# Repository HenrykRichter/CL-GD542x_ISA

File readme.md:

# Project  Cirrus Logic 542x ISA video card
This project is a fork of [542x_ISA](https://github.com/matt1187/542x_ISA) with some tweaks
and additions to the PCB. Notable changes compared to original project:
- made room on PCB to place the RAMs in SMT sockets
- added Monitor ID option (static or by attached Monitor)

Remaking from Cirrus Logic Databook  "CL-GD542X_Technical_Reference_Manual_Jan1994"

# PCB Revision History 
- forked from revision 001
- CL-GD542x-003 initial upload

# Features
- Cirrus Logic (CL-GD5422-5429) video chipset (5420 is not recommend for this design)
- good chocie video card for ISA bus platform
- up to 2 MB DRAM
- 80 MHz integrated RAMDAC (GD5429: 86 MHz )
- Win 3.1, Win9x, Win NT 3.51 & 4 driver available
- cheap GD542x VLB card as compoment donor.
- cheap 2 layer PCB layout 
  
# Issues 
- some 542x chip has vertical noise/stripe on TFT. (It is not pcb issuses)
- ROM from  cirrus logic video card as donor is not usable (hi/lo byte is seperated to difference address space, like address line "A0 and A14" is swapped)
- in some cases, the GD542x will boot in Monochrome mode. See [here](https://forum.vcfed.org/index.php?threads/trident-card-that-thinks-colour-monitor-is-monochrome.79054) for a fix.

# notes
- GD5420/22/24 support only 1 MB DRAM
- U11 & U12  is first 1 MB , U13/14 is seconds MB (except 5420, only U12 and U14 )
- all component with  followed ID is config strap (R55, R57, R59, R61, R63, R69, R73) place all **except** R55, R69
- R15 don't place, if you using interal XTAL oscillator (Y1/Y2 , C39,C40)
- Place only one of Y1/Y2 (either SMD **or** HC-49)
- SPI-EEPROM is optional.

# Bill of material

- see BOM subfolder for an iBOM file

# driver & ROM 
- []

# License
The project is free for non-commercial reproduction. Do not sell it on Ebay or other platforms for profit. Do not make a closed source derivative. Share your experiences and ideas with the community.

This work is licensed under a [Creative Commons Attribution-NonCommercial-ShareAlike 4.0 International License][cc-by-nc-sa].

[![CC BY-NC-SA 4.0][cc-by-nc-sa-image]][cc-by-nc-sa]

[cc-by-nc-sa]: http://creativecommons.org/licenses/by-nc-sa/4.0/
[cc-by-nc-sa-image]: https://licensebuttons.net/l/by-nc-sa/4.0/88x31.png

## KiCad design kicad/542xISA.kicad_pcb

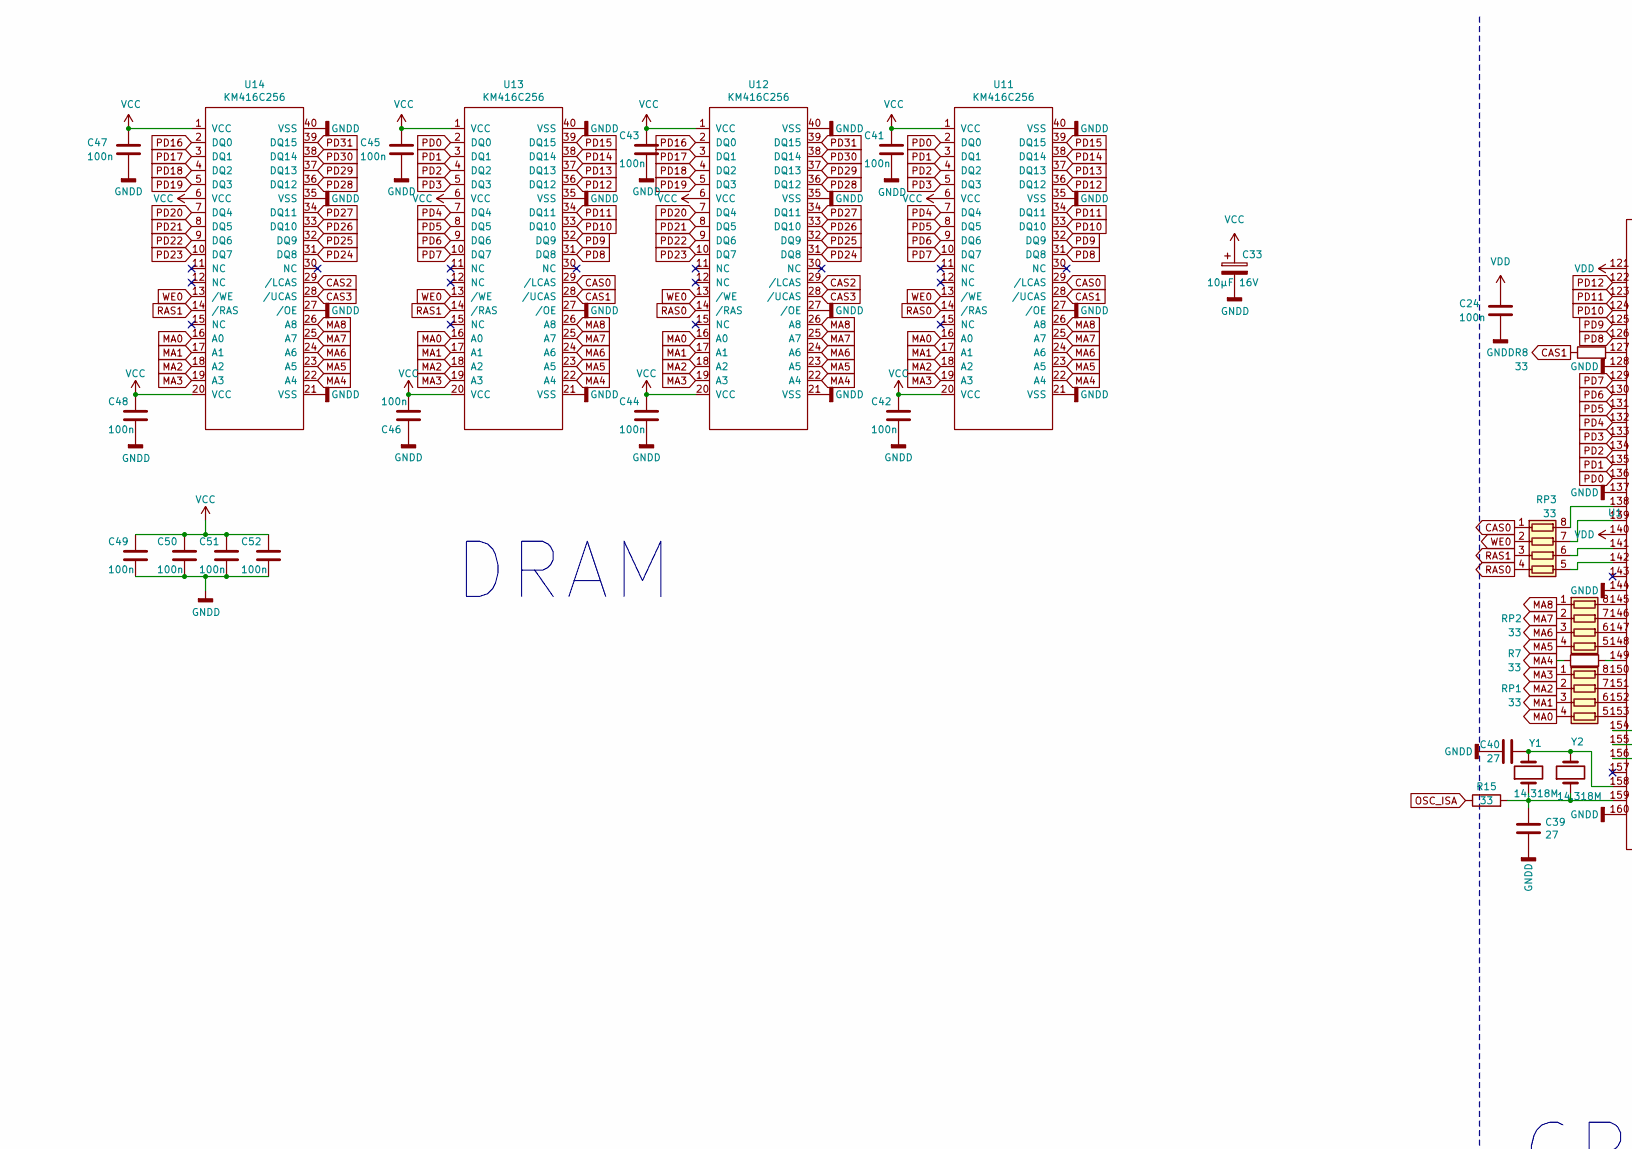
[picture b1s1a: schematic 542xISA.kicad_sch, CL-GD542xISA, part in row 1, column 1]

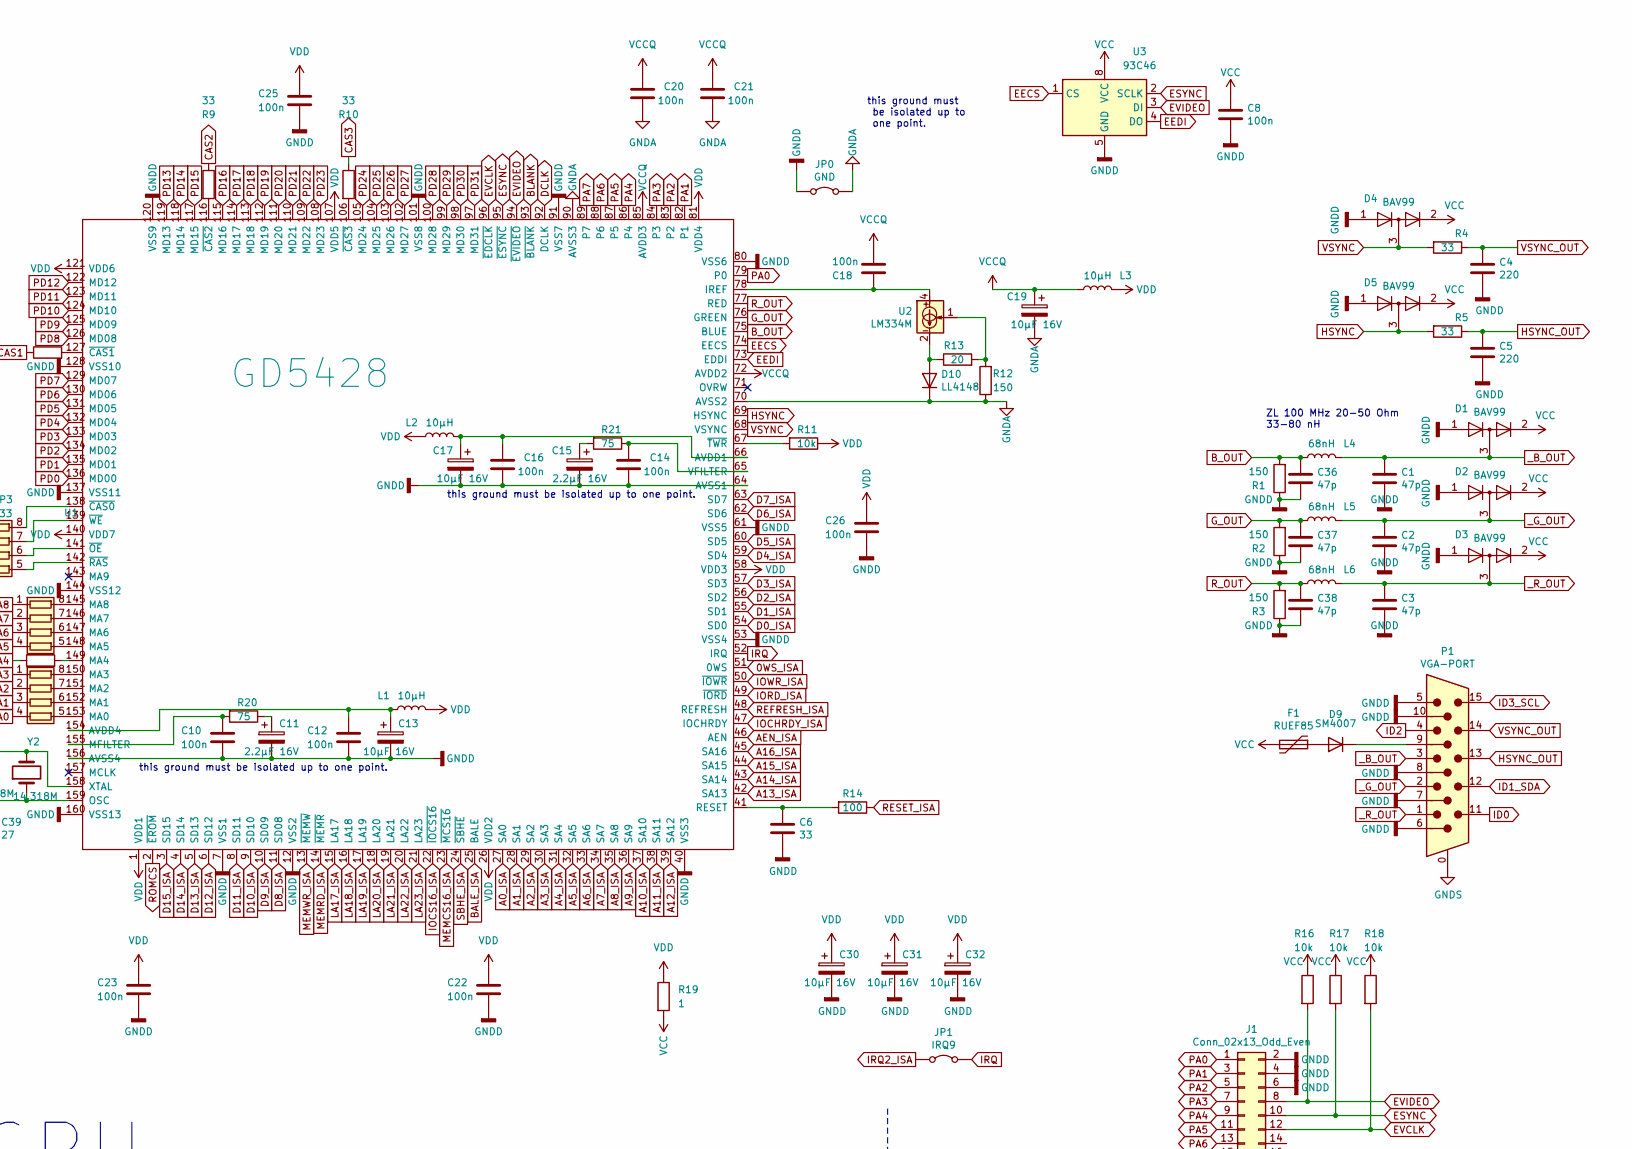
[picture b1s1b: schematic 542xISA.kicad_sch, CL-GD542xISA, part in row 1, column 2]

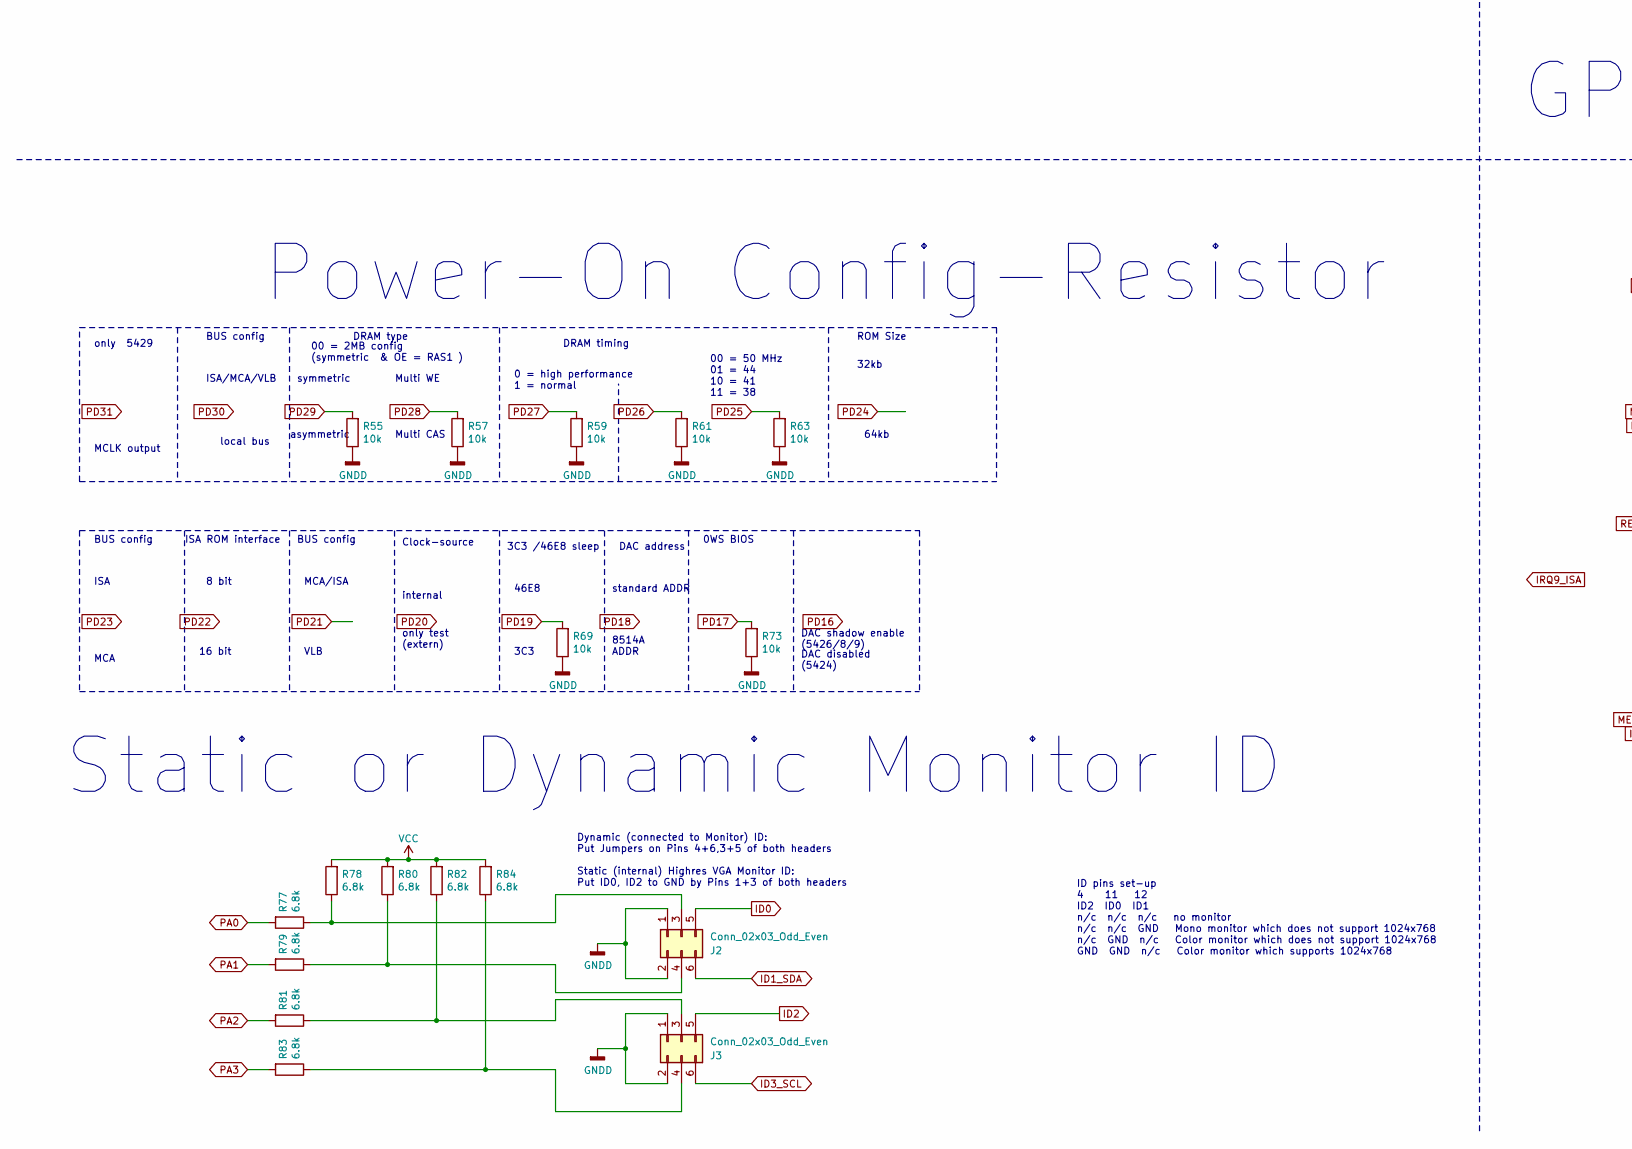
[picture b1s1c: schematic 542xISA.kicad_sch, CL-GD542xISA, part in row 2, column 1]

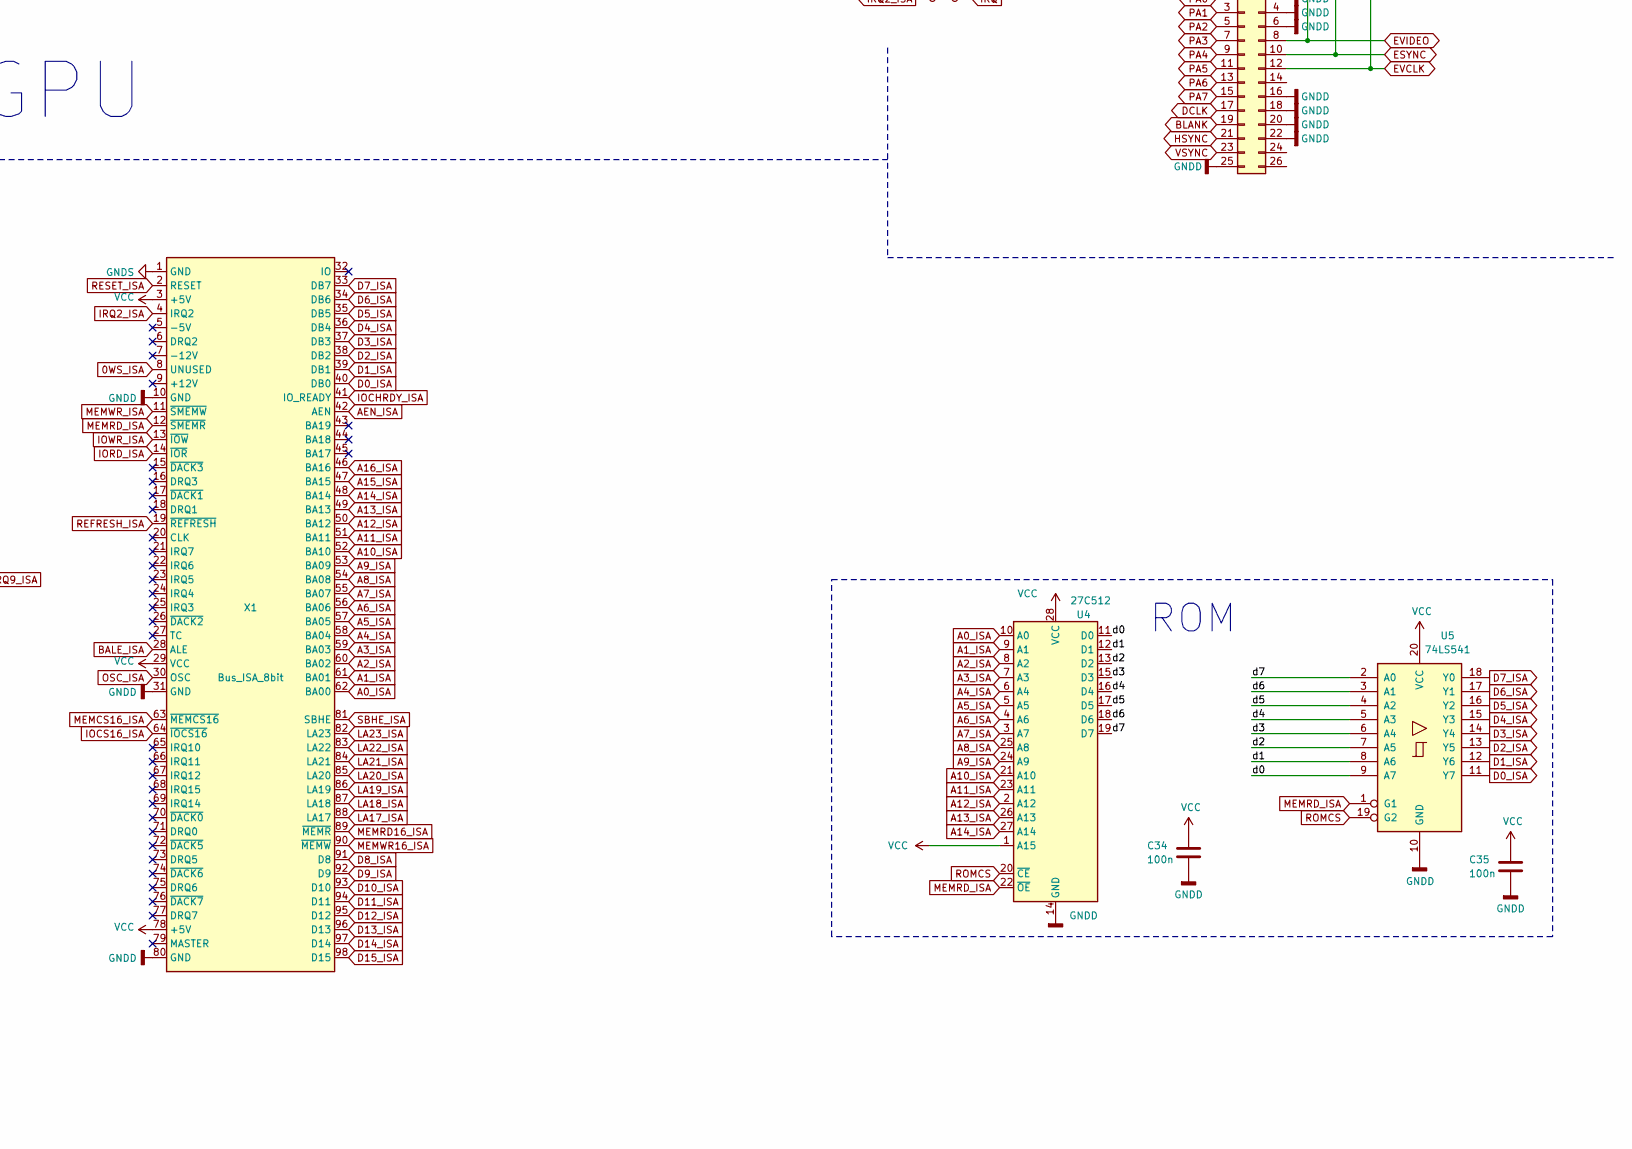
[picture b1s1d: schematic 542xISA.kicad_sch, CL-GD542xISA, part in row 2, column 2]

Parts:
C1, C2, C3, C36, C37, C38: 47p; C_0805_2012Metric
C4, C5: 220; C_0805_2012Metric
C6: 33; C_0805_2012Metric
C8, C10, C12, C14, C16, C18, C20, C21, C22, C23, C24, C25, C26, C34, C35, C41, C42, C43, C44, C45, C46, C47, C48, C49, C50, C51, C52: 100n; C_0805_2012Metric
C11, C15: 2.2µF 16V; CP_EIA-3528-12_Kemet-T
C13, C17, C19, C31, C32: 10µF 16V; CP_EIA-6032-15_Kemet-U
C30, C33: 10µF 16V; C_0805_2012Metric_Pad1.18x1.45mm_HandSolder
C39, C40: 27; C_0805_2012Metric
D1, D2, D3, D4, D5: BAV99; SOT-23
D9: SM4007; D_MELF
D10: LL4148; D_MiniMELF
F1: RUEF85; Fuse_Bourns_MF-RG300
J1: Conn_02x13_Odd_Even; PinHeader_2x13_P2.54mm_Vertical
J2, J3: Conn_02x03_Odd_Even; PinHeader_2x03_P2.54mm_Vertical
JP0: GND; SolderJumper-2_P1.3mm_Bridged2Bar_Pad1.0x1.5mm
JP1: IRQ9; PinHeader_1x02_P2.54mm_Vertical
L1, L2, L3: 10µH; L_0805_2012Metric
L4, L5, L6: 68nH; L_1206_3216Metric
P1: VGA-PORT; DSUB-15-HD_Female_Horizontal_P2.29x1.98mm_EdgePinOffset8.35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
R1, R2, R3, R12: 150; R_0805_2012Metric
R4, R5, R7, R8, R9, R10, R15: 33; R_0805_2012Metric
R11, R16, R17, R18, R55, R57, R59, R61, R63, R69, R73: 10k; R_0805_2012Metric
R13: 20; R_0805_2012Metric
R14: 100; R_0805_2012Metric
R19: 1; R_0805_2012Metric
R20, R21: 75; R_0805_2012Metric
R77, R78, R79, R80, R81, R82, R83, R84: 6.8k; R_0805_2012Metric
RP1, RP2, RP3: 33; R_Array_Concave_4x0603
U1: GD5428; PQFP-160_28x28mm_P0.65mm
U2: LM334M; SOIC-8_3.9x4.9mm_P1.27mm
U3: 93C46; SOIC-8_3.9x4.9mm_P1.27mm
U4: 27C512; DIP-28_W15.24mm_Socket
U5: 74LS541; SOIC-20W_7.5x12.8mm_P1.27mm
U11, U12, U13, U14: KM416C256; SOJ-40-Socket
X1: Bus_ISA_8bit; BUS_AT
Y1: 14.318M; Crystal_SMD_0603-2Pin_6.0x3.5mm
Y2: 14.318M; Crystal_HC49-U_Vertical

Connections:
0WS_ISA: U1.51 (0WS), X1.8 (UNUSED)
/d0: U4.11 (D0), U5.9 (A7)
/d1: U4.12 (D1), U5.8 (A6)
/d2: U4.13 (D2), U5.7 (A5)
/d3: U4.15 (D3), U5.6 (A4)
/d4: U4.16 (D4), U5.5 (A3)
/d5: U4.17 (D5), U5.4 (A2)
/d6: U4.18 (D6), U5.3 (A1)
/d7: U4.19 (D7), U5.2 (A0)
A0_ISA: U1.27 (SA0), U4.10 (A0), X1.62 (BA00)
A1_ISA: U1.28 (SA1), U4.9 (A1), X1.61 (BA01)
A2_ISA: U1.29 (SA2), U4.8 (A2), X1.60 (BA02)
A3_ISA: U1.30 (SA3), U4.7 (A3), X1.59 (BA03)
A4_ISA: U1.31 (SA4), U4.6 (A4), X1.58 (BA04)
A5_ISA: U1.32 (SA5), U4.5 (A5), X1.57 (BA05)
A6_ISA: U1.33 (SA6), U4.4 (A6), X1.56 (BA06)
A7_ISA: U1.34 (SA7), U4.3 (A7), X1.55 (BA07)
A8_ISA: U1.35 (SA8), U4.25 (A8), X1.54 (BA08)
A9_ISA: U1.36 (SA9), U4.24 (A9), X1.53 (BA09)
A10_ISA: U1.37 (SA10), U4.21 (A10), X1.52 (BA10)
A11_ISA: U1.38 (SA11), U4.23 (A11), X1.51 (BA11)
A12_ISA: U1.39 (SA12), U4.2 (A12), X1.50 (BA12)
A13_ISA: U1.42 (SA13), U4.26 (A13), X1.49 (BA13)
A14_ISA: U1.43 (SA14), U4.27 (A14), X1.48 (BA14)
A15_ISA: U1.44 (SA15), X1.47 (BA15)
A16_ISA: U1.45 (SA16), X1.46 (BA16)
AEN_ISA: U1.46 (AEN), X1.42 (AEN)
BALE_ISA: U1.25 (BALE), X1.28 (ALE)
BLANK: J1.19, U1.93 (~BLANK)
B_OUT: C36.1, L4.2, R1.2, U1.75 (BLUE)
CAS0: RP3.1 (R1.1), U11.29 (/LCAS), U13.29 (/LCAS)
CAS1: R8.1, U11.28 (/UCAS), U13.28 (/UCAS)
CAS2: R9.1, U12.29 (/LCAS), U14.29 (/LCAS)
CAS3: R10.1, U12.28 (/UCAS), U14.28 (/UCAS)
D0_ISA: U1.54 (SD0), U5.11 (Y7), X1.40 (DB0)
D1_ISA: U1.55 (SD1), U5.12 (Y6), X1.39 (DB1)
D2_ISA: U1.56 (SD2), U5.13 (Y5), X1.38 (DB2)
D3_ISA: U1.57 (SD3), U5.14 (Y4), X1.37 (DB3)
D4_ISA: U1.59 (SD4), U5.15 (Y3), X1.36 (DB4)
D5_ISA: U1.60 (SD5), U5.16 (Y2), X1.35 (DB5)
D6_ISA: U1.62 (SD6), U5.17 (Y1), X1.34 (DB6)
D7_ISA: U1.63 (SD7), U5.18 (Y0), X1.33 (DB7)
D8_ISA: U1.11 (SD08), X1.91 (D8)
D9_ISA: U1.10 (SD09), X1.92 (D9)
D10_ISA: U1.9 (SD10), X1.93 (D10)
D11_ISA: U1.8 (SD11), X1.94 (D11)
D12_ISA: U1.6 (SD12), X1.95 (D12)
D13_ISA: U1.5 (SD13), X1.96 (D13)
D14_ISA: U1.4 (SD14), X1.97 (D14)
D15_ISA: U1.3 (SD15), X1.98 (D15)
DCLK: J1.17, U1.92 (DCLK)
EECS: U1.74 (EECS), U3.1 (CS)
EEDI: U1.73 (EDDI), U3.4 (DO)
ESYNC: J1.10, R17.2, U1.95 (~ESYNC), U3.2 (SCLK)
EVCLK: J1.12, R18.2, U1.96 (~EDCLK)
EVIDEO: J1.8, R16.2, U1.94 (~EVIDEO), U3.3 (DI)
GNDA: C19.2, C20.2, C21.2, D10.1 (K), JP0.2 (B), R12.1, U1.70 (AVSS2), U1.90 (AVSS3)
GNDD: C1.2, C2.2, C3.2, C4.2, C5.2, C6.2, C8.2, C10.2, C11.2, C12.2, C13.2, C14.2, C15.2, C16.2, C17.2, C22.2, C23.2, C24.2, C25.2, C26.2, C30.2, C31.2, C32.2, C33.2, C34.2, C35.2, C36.2, C37.2, C38.2, C39.2, C40.1, C41.2, C42.2, C43.2, C44.2, C45.2, C46.2, C47.2, C48.2, C49.2, C50.2, C51.2, C52.2, D1.1 (K), D2.1 (K), D3.1 (K), D4.1 (K), D5.1 (K), J1.2, J1.4, J1.6, J1.16, J1.18, J1.20, J1.22, J1.25, J2.1, J2.2, J3.1, J3.2, JP0.1 (A), P1.5, P1.6, P1.7, P1.8, P1.10, R1.1, R2.1, R3.1, R55.1, R57.1, R59.1, R61.1, R63.1, R69.1, R73.1, U1.7 (VSS1), U1.12 (VSS2), U1.40 (VSS3), U1.53 (VSS4), U1.61 (VSS5), U1.64 (AVSS1), U1.80 (VSS6), U1.91 (VSS7), U1.101 (VSS8), U1.120 (VSS9), U1.128 (VSS10), U1.137 (VSS11), U1.144 (VSS12), U1.156 (AVSS4), U1.160 (VSS13), U3.5 (GND), U4.14 (GND), U5.10 (GND), U11.21 (VSS), U11.27 (/OE), U11.35 (VSS), U11.40 (VSS), U12.21 (VSS), U12.27 (/OE), U12.35 (VSS), U12.40 (VSS), U13.21 (VSS), U13.27 (/OE), U13.35 (VSS), U13.40 (VSS), U14.21 (VSS), U14.27 (/OE), U14.35 (VSS), U14.40 (VSS), X1.10 (GND), X1.31 (GND), X1.80 (GND)
GNDS: P1.0, X1.1 (GND)
G_OUT: C37.1, L5.2, R2.2, U1.76 (GREEN)
HSYNC: D5.3 (K), J1.21, R5.2, U1.69 (HSYNC)
HSYNC_OUT: C5.1, P1.13, R5.1
ID0: J2.5, P1.11
ID1_SDA: J2.6, P1.12
ID2: J3.5, P1.4
ID3_SCL: J3.6, P1.15
IOCHRDY_ISA: U1.47 (IOCHRDY), X1.41 (IO_READY)
IOCS16_ISA: U1.22 (~IOCS16), X1.64 (~IOCS16)
IORD_ISA: U1.49 (~IORD), X1.14 (~IOR)
IOWR_ISA: U1.50 (~IOWR), X1.13 (~IOW)
IRQ: JP1.2 (B), U1.52 (IRQ)
IRQ2_ISA: JP1.1 (A), X1.4 (IRQ2)
LA17_ISA: U1.15 (LA17), X1.88 (LA17)
LA18_ISA: U1.16 (LA18), X1.87 (LA18)
LA19_ISA: U1.17 (LA19), X1.86 (LA19)
LA20_ISA: U1.18 (LA20), X1.85 (LA20)
LA21_ISA: U1.19 (LA21), X1.84 (LA21)
LA22_ISA: U1.20 (LA22), X1.83 (LA22)
LA23_ISA: U1.21 (LA23), X1.82 (LA23)
MA0: RP1.4 (R4.1), U11.16 (A0), U12.16 (A0), U13.16 (A0), U14.16 (A0)
MA1: RP1.3 (R3.1), U11.17 (A1), U12.17 (A1), U13.17 (A1), U14.17 (A1)
MA2: RP1.2 (R2.1), U11.18 (A2), U12.18 (A2), U13.18 (A2), U14.18 (A2)
MA3: RP1.1 (R1.1), U11.19 (A3), U12.19 (A3), U13.19 (A3), U14.19 (A3)
MA4: R7.1, U11.22 (A4), U12.22 (A4), U13.22 (A4), U14.22 (A4)
MA5: RP2.4 (R4.1), U11.23 (A5), U12.23 (A5), U13.23 (A5), U14.23 (A5)
MA6: RP2.3 (R3.1), U11.24 (A6), U12.24 (A6), U13.24 (A6), U14.24 (A6)
MA7: RP2.2 (R2.1), U11.25 (A7), U12.25 (A7), U13.25 (A7), U14.25 (A7)
MA8: RP2.1 (R1.1), U11.26 (A8), U12.26 (A8), U13.26 (A8), U14.26 (A8)
MEMCS16_ISA: U1.23 (~MCS16), X1.63 (~MEMCS16)
MEMRD16_ISA: X1.89 (~MEMR)
MEMRD_ISA: U1.14 (~MEMR), U4.22 (~OE), U5.1 (G1), X1.12 (~SMEMR)
MEMWR16_ISA: X1.90 (~MEMW)
MEMWR_ISA: U1.13 (~MEMW), X1.11 (~SMEMW)
unnamed: C11.1, R20.1
unnamed: C15.1, R21.2
unnamed: D9.2 (A), F1.1
unnamed: D9.1 (K), P1.9
unnamed: D10.2 (A), R13.1, U2.2, U2.3, U2.6, U2.7
unnamed: J2.3, R77.1, R78.1
unnamed: J2.4, R79.1, R80.1
unnamed: J3.3, R81.1, R82.1
unnamed: J3.4, R83.1, R84.1
unnamed: R12.2, R13.2, U2.1
unnamed: RP1.8 (R1.2), U1.150 (MA3)
unnamed: RP1.7 (R2.2), U1.151 (MA2)
unnamed: RP1.6 (R3.2), U1.152 (MA1)
unnamed: RP1.5 (R4.2), U1.153 (MA0)
unnamed: RP2.8 (R1.2), U1.145 (MA8)
unnamed: RP2.7 (R2.2), U1.146 (MA7)
unnamed: RP2.6 (R3.2), U1.147 (MA6)
unnamed: RP2.5 (R4.2), U1.148 (MA5)
unnamed: RP3.8 (R1.2), U1.138 (~CAS0)
unnamed: RP3.7 (R2.2), U1.139 (~WE)
unnamed: RP3.6 (R3.2), U1.141 (~OE)
unnamed: RP3.5 (R4.2), U1.142 (~RAS)
unnamed: C16.1, C17.1, L2.2, U1.66 (AVDD1)
unnamed: C12.1, C13.1, L1.1, U1.154 (AVDD4)
unnamed: C18.1, U1.78 (IREF), U2.4
unnamed: R7.2, U1.149 (MA4)
unnamed: C10.1, R20.2, U1.155 (MFILTER)
unnamed: C39.1, R15.2, U1.159 (OSC), Y1.1, Y2.1
unnamed: C6.1, R14.2, U1.41 (RESET)
unnamed: C14.1, R21.1, U1.65 (VFILTER)
unnamed: C40.2, U1.158 (XTAL), Y1.2, Y2.2
unnamed: R8.2, U1.127 (~CAS1)
unnamed: R9.2, U1.116 (~CAS2)
unnamed: R10.2, U1.106 (~CAS3)
unnamed: R11.2, U1.67 (~TWR)
OSC_ISA: R15.1, X1.30 (OSC)
PA0: J1.1, R77.2, U1.79 (P0)
PA1: J1.3, R79.2, U1.82 (P1)
PA2: J1.5, R81.2, U1.83 (P2)
PA3: J1.7, R83.2, U1.84 (P3)
PA4: J1.9, U1.86 (P4)
PA5: J1.11, U1.87 (P5)
PA6: J1.13, U1.88 (P6)
PA7: J1.15, U1.89 (P7)
PD0: U1.136 (MD00), U11.2 (DQ0), U13.2 (DQ0)
PD1: U1.135 (MD01), U11.3 (DQ1), U13.3 (DQ1)
PD2: U1.134 (MD02), U11.4 (DQ2), U13.4 (DQ2)
PD3: U1.133 (MD03), U11.5 (DQ3), U13.5 (DQ3)
PD4: U1.132 (MD04), U11.7 (DQ4), U13.7 (DQ4)
PD5: U1.131 (MD05), U11.8 (DQ5), U13.8 (DQ5)
PD6: U1.130 (MD06), U11.9 (DQ6), U13.9 (DQ6)
PD7: U1.129 (MD07), U11.10 (DQ7), U13.10 (DQ7)
PD8: U1.126 (MD08), U11.31 (DQ8), U13.31 (DQ8)
PD9: U1.125 (MD09), U11.32 (DQ9), U13.32 (DQ9)
PD10: U1.124 (MD10), U11.33 (DQ10), U13.33 (DQ10)
PD11: U1.123 (MD11), U11.34 (DQ11), U13.34 (DQ11)
PD12: U1.122 (MD12), U11.36 (DQ12), U13.36 (DQ12)
PD13: U1.119 (MD13), U11.37 (DQ13), U13.37 (DQ13)
PD14: U1.118 (MD14), U11.38 (DQ14), U13.38 (DQ14)
PD15: U1.117 (MD15), U11.39 (DQ15), U13.39 (DQ15)
PD16: U1.115 (MD16), U12.2 (DQ0), U14.2 (DQ0)
PD17: R73.2, U1.114 (MD17), U12.3 (DQ1), U14.3 (DQ1)
PD18: U1.113 (MD18), U12.4 (DQ2), U14.4 (DQ2)
PD19: R69.2, U1.112 (MD19), U12.5 (DQ3), U14.5 (DQ3)
PD20: U1.111 (MD20), U12.7 (DQ4), U14.7 (DQ4)
PD21: U1.110 (MD21), U12.8 (DQ5), U14.8 (DQ5)
PD22: U1.109 (MD22), U12.9 (DQ6), U14.9 (DQ6)
PD23: U1.108 (MD23), U12.10 (DQ7), U14.10 (DQ7)
PD24: U1.105 (MD24), U12.31 (DQ8), U14.31 (DQ8)
PD25: R63.2, U1.104 (MD25), U12.32 (DQ9), U14.32 (DQ9)
PD26: R61.2, U1.103 (MD26), U12.33 (DQ10), U14.33 (DQ10)
PD27: R59.2, U1.102 (MD27), U12.34 (DQ11), U14.34 (DQ11)
PD28: R57.2, U1.100 (MD28), U12.36 (DQ12), U14.36 (DQ12)
PD29: R55.2, U1.99 (MD29), U12.37 (DQ13), U14.37 (DQ13)
PD30: U1.98 (MD30), U12.38 (DQ14), U14.38 (DQ14)
PD31: U1.97 (MD31), U12.39 (DQ15), U14.39 (DQ15)
RAS0: RP3.4 (R4.1), U11.14 (/RAS), U12.14 (/RAS)
RAS1: RP3.3 (R3.1), U13.14 (/RAS), U14.14 (/RAS)
REFRESH_ISA: U1.48 (REFRESH), X1.19 (~REFRESH)
RESET_ISA: R14.1, X1.2 (RESET)
ROMCS: U1.2 (~EROM), U4.20 (~CE), U5.19 (G2)
R_OUT: C38.1, L6.2, R3.2, U1.77 (RED)
SBHE_ISA: U1.24 (~SBHE), X1.81 (SBHE)
VCC: C8.1, C33.1, C34.1, C35.1, C41.1, C42.1, C43.1, C44.1, C45.1, C46.1, C47.1, C48.1, C49.1, C50.1, C51.1, C52.1, D1.2 (A), D2.2 (A), D3.2 (A), D4.2 (A), D5.2 (A), F1.2, R16.1, R17.1, R18.1, R19.2, R78.2, R80.2, R82.2, R84.2, U3.8 (VCC), U4.1 (A15), U4.28 (VCC), U5.20 (VCC), U11.1 (VCC), U11.6 (VCC), U11.20 (VCC), U12.1 (VCC), U12.6 (VCC), U12.20 (VCC), U13.1 (VCC), U13.6 (VCC), U13.20 (VCC), U14.1 (VCC), U14.6 (VCC), U14.20 (VCC), X1.3 (+5V), X1.29 (VCC), X1.78 (+5V)
VCCQ: C18.2, C19.1, C20.1, C21.1, L3.2, U1.72 (AVDD2), U1.85 (AVDD3)
VDD: C22.1, C23.1, C24.1, C25.1, C26.1, C30.1, C31.1, C32.1, L1.2, L2.1, L3.1, R11.1, R19.1, U1.1 (VDD1), U1.26 (VDD2), U1.58 (VDD3), U1.81 (VDD4), U1.107 (VDD5), U1.121 (VDD6), U1.140 (VDD7)
VSYNC: D4.3 (K), J1.23, R4.2, U1.68 (VSYNC)
VSYNC_OUT: C4.1, P1.14, R4.1
WE0: RP3.2 (R2.1), U11.13 (/WE), U12.13 (/WE), U13.13 (/WE), U14.13 (/WE)
_B_OUT: C1.1, D1.3 (K), L4.1, P1.3
_G_OUT: C2.1, D2.3 (K), L5.1, P1.2
_R_OUT: C3.1, D3.3 (K), L6.1, P1.1

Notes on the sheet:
asymmetric
BUS config
this ground must be isolated up to one point.
VLB
standard ADDR
DRAM timing
MCLK output
00 = 2MB config (symmetric & OE = RAS1 )
8 bit
DAC disabled (5424)
Dynamic (connected to Monitor) ID: Put Jumpers on Pins 4+6,3+5 of both headers Static (internal) Highres VGA Monitor ID: Put ID0, ID2 to GND by Pins 1+3 of both headers
only test (extern)
ROM Size
DAC shadow enable (5426/8/9)
0 = high performance 1 = normal
32kb
46E8
this ground must be isolated up to one point.
ISA/MCA/VLB
ISA ROM interface
Multi WE
Clock-source
ROM
3C3 /46E8 sleep
ID pins set-up 4 11 12 ID2 ID0 ID1 n/c n/c n/c no monitor n/c n/c GND Mono monitor which does not support 1024x768 n/c GND n/c Color monitor which does not support 1024x768 GND GND n/c Color monitor which supports 1024x768
Static or Dynamic Monitor ID
DRAM type
ZL 100 MHz 20-50 Ohm 33-80 nH
DRAM
only 5429
MCA
symmetric
local bus
GPU
00 = 50 MHz 01 = 44 10 = 41 11 = 38
0WS BIOS
64kb
DAC address
internal
16 bit

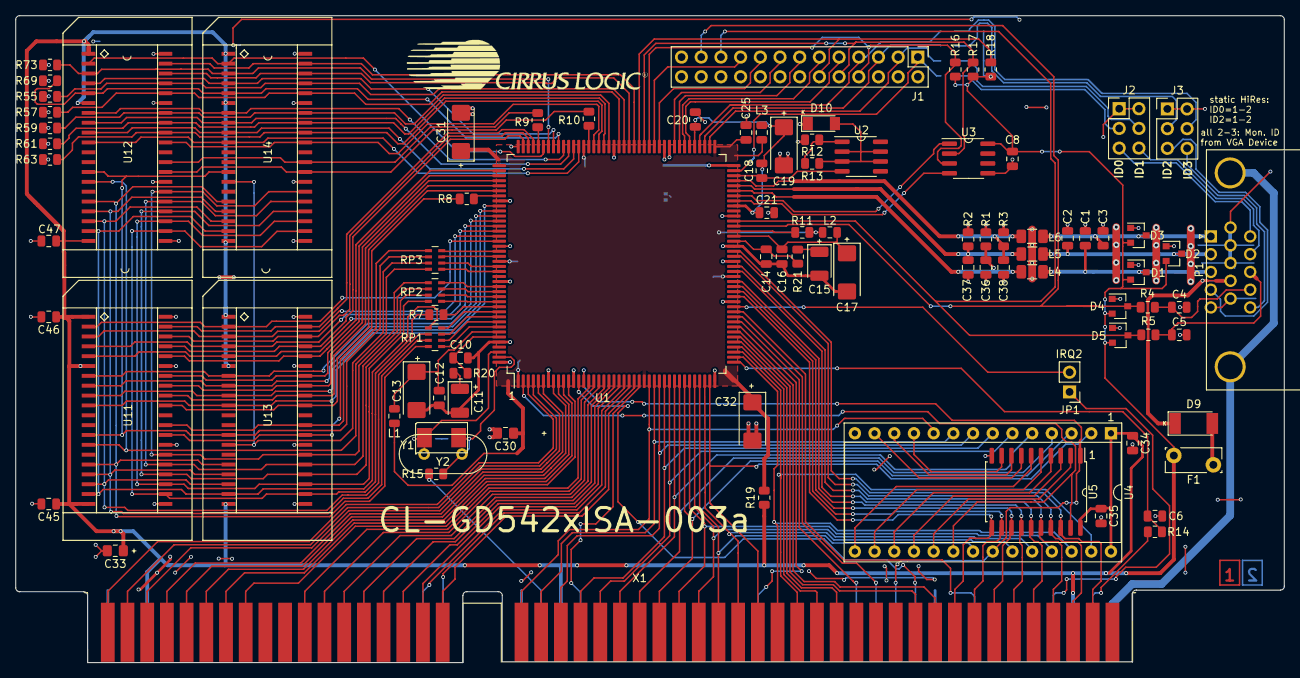
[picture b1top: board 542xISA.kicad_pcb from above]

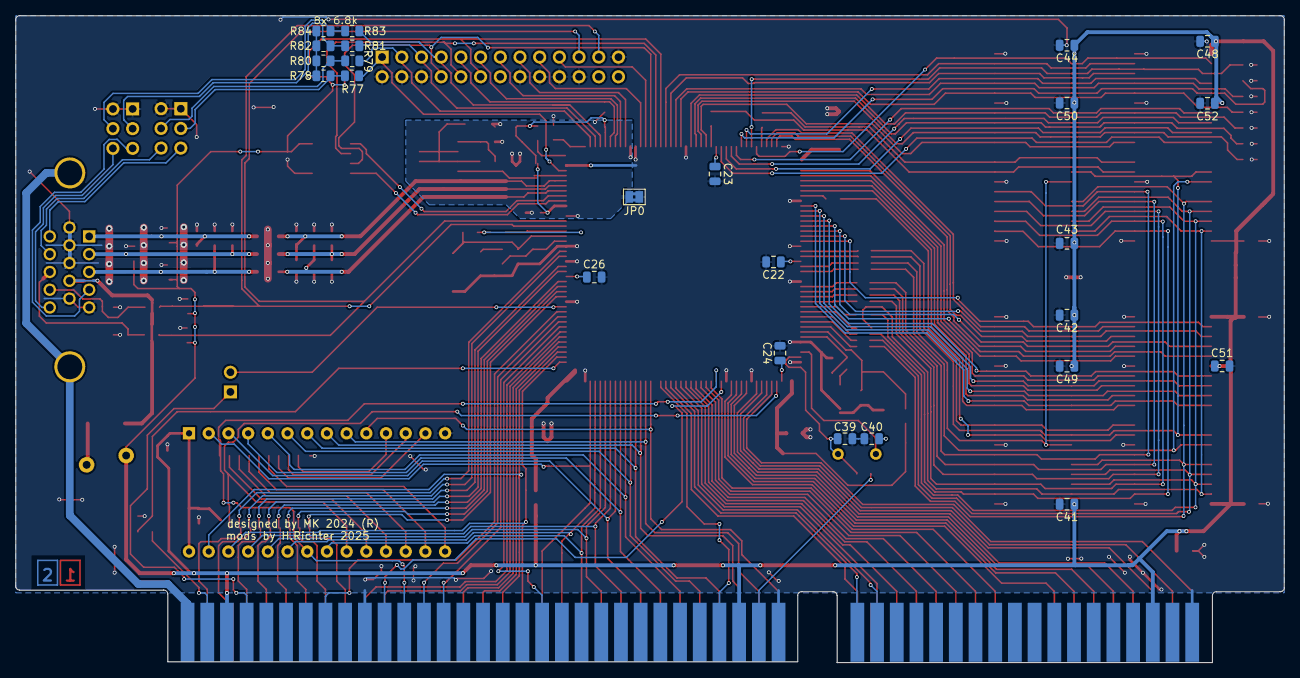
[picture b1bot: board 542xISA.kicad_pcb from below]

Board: 2 copper layers, 163.6 x 83.4 mm, 118 parts (24 on the bottom side), 183 nets.

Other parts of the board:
Cirrus1: (no value)

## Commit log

2025-11-11 v0.3, socketed RAM support, Monitor ID support
